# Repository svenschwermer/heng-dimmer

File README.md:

# Heng Balance Lamp Dimmer
This is a simple dimmer module that is designed for the Heng Balance Lamp that
materialized on [Kickstarter][1] a while back and is available through various
distributors.

## Circuit
The circuit was designed with components that I had at hand at the time.
Luckily, the lamp is powered via a USB power supply, so I could just pulse width
modulate the supply to the lamp in line. The switching transistor is a
[BUZ11][2] N-channel MOSFET. It's driven directly by one of the output compare
pins of the [ATtiny13A][3].

The user adjusts the PWM duty cycle (i.e. brightness) via a rotary encoder that
includes a push button switch. The wires are soldered directly to the underside
of the circuit board. Holes allow to install cable ties as strain relief.

The PCB is shared on [OSH Park][4].

## Firmware
The program configures the timer to run in fast PWM mode with a prescaler of 8.
Since I didn't change the clocking fuses, the microcontroller runs at 1.2MHz.
With the prescaler and the 8 bit resolution, the PWM frequency ends up being
586Hz which is sufficient to not see flicker.

7 distinct brightness levels can be selected by turning the rotary encoder.
Pushing it brings the lamp to full brightness if it wasn't already. It switches
the lamp completely off otherwise. This allows toggling between off and fully on
by pushing the button.

The encoder phase and button inputs are sampled every time the timer overflows,
i.e. with the same frequency as the PWM frequency. The button is debounced by
requiring it to be pushed for > 107ms.

*Note:* When the JTAGICE3 is attached to the board, the push button
functionality doesn't work reliably since the programmer seems to include a
pull-up resistor on the SCK line.

## Housing
The housing allows the populated circuit board to be fastened by the rotary
encoder nut. Unfortunately, the design doesn't allow the PCB to be taken out
once the cables are installed. Neither is it possible to access the programming
header once the cables are installed and the PCB is installed in the housing.

The big radius on the back side allows to fasten the entire unit to the round
base of the lamp using cable ties.

## Pictures

[1]:https://www.kickstarter.com/projects/1458079400/heng-balance-lamp-a-unique-lamp-with-switch-in-mid
[2]:https://www.onsemi.com/pub/Collateral/BUZ11-D.PDF
[3]:http://ww1.microchip.com/downloads/en/DeviceDoc/doc8126.pdf
[4]:https://oshpark.com/shared_projects/AtPNl2Sx

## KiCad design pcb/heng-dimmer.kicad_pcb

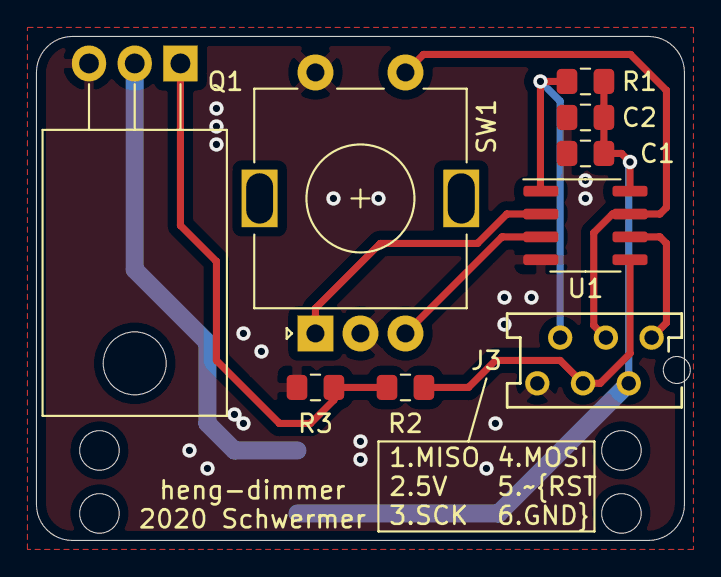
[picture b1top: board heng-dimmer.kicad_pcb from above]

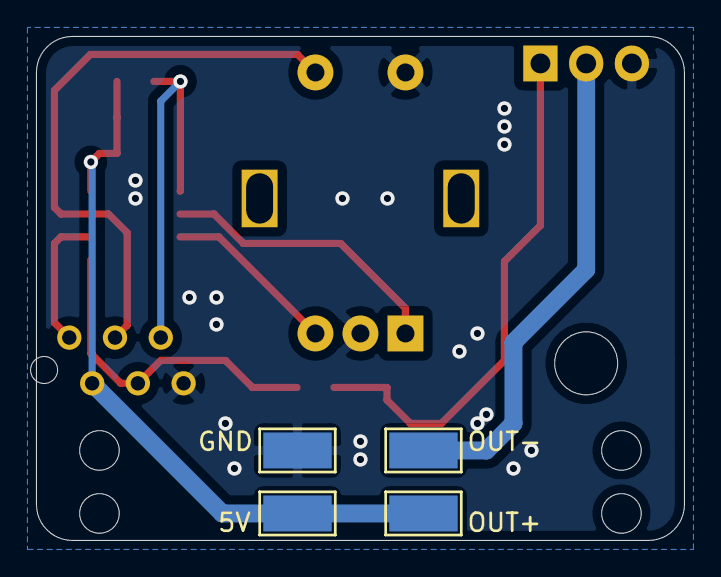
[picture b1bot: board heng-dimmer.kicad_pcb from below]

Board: 2 copper layers, 36.0 x 28.0 mm, 17 parts (4 on the bottom side), 10 nets.

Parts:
C1: 100n; C_0805_2012Metric_Pad1.15x1.40mm_HandSolder
C2: 10µ; C_0805_2012Metric_Pad1.15x1.40mm_HandSolder
H1, H2, H3, H4: MountingHole; MountingHole_2.2mm_M2
J1: 5V; TestPoint_Keystone_5019_Minature
J2: GND; TestPoint_Keystone_5019_Minature
J3: dW (SPI); TE_MICRO-MATCH_FOB.06P
J4: OUT+; TestPoint_Keystone_5019_Minature
J5: OUT-; TestPoint_Keystone_5019_Minature
Q1: BUZ11; TO-220-3_Horizontal_TabDown
R1, R3: 10k; R_0805_2012Metric_Pad1.15x1.40mm_HandSolder
R2: 100; R_0805_2012Metric_Pad1.15x1.40mm_HandSolder
SW1: Rotary_Encoder_Switch; RotaryEncoder_Alps_EC11E-Switch_Vertical_H20mm
U1: ATtiny13A-SSU; SOIC-8_3.9x4.9mm_P1.27mm

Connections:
+5V: C1.1, C2.1, J1.1, J3.2, J4.1, R1.1, U1.8
/MISO: J3.1, U1.6
/MOSI: J3.4, R2.2, U1.5
/SCK: J3.3, SW1.S1, U1.7
/~RESET: J3.5, R1.2, U1.1
GND: C1.2, C2.2, J2.1, J3.6, Q1.3, R3.2, SW1.C, SW1.S2, U1.4
unnamed: J5.1, Q1.2
unnamed: Q1.1, R2.1, R3.1
unnamed: SW1.A, U1.2
unnamed: SW1.B, U1.3

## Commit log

2020-01-30 Initial
2020-02-01 Add readme
2020-02-01 Add license
2020-02-01 Add PDF schematics
2020-02-02 Add OSH Park link
